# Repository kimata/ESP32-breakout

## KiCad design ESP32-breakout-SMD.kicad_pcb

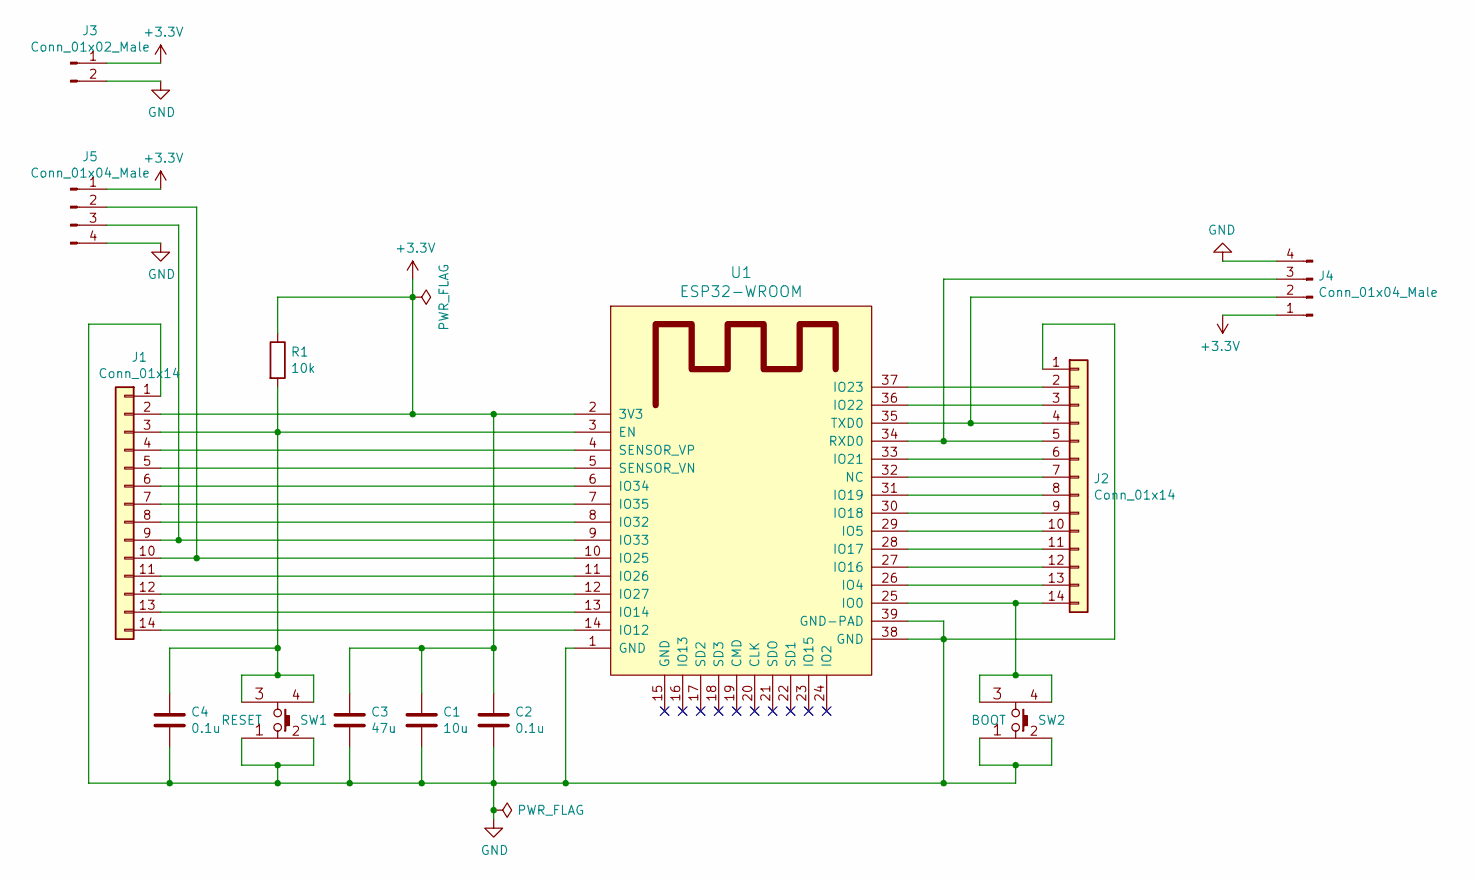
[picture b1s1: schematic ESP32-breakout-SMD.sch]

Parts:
C1: 10u; C_0805_2012Metric_Pad1.15x1.40mm_HandSolder
C2, C4: 0.1u; C_0805_2012Metric_Pad1.15x1.40mm_HandSolder
C3: 47u; C_1206_3216Metric_Pad1.42x1.75mm_HandSolder
J1, J2: Conn_01x14; PinHeader_1x14_P2.54mm_Vertical
J3: Conn_01x02_Male; JST_PH_S2B-PH-SM4-TB_1x02-1MP_P2.00mm_Horizontal
J4, J5: Conn_01x04_Male; JST_PH_S4B-PH-SM4-TB_1x04-1MP_P2.00mm_Horizontal
R1: 10k; R_0805_2012Metric_Pad1.15x1.40mm_HandSolder
SW1: RESET; SKRPACE010
SW2: BOOT; SKRPACE010
U1: ESP32-WROOM

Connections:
+3V3: C1.1, C2.1, C3.1, J1.2, J3.1, J4.1, J5.1, R1.1, U1.2 (3V3)
GND: C1.2, C2.2, C3.2, C4.2, J1.1, J2.1, J3.2, J4.4, J5.4, SW1.1, SW1.2, SW2.1, SW2.2, U1.1 (GND), U1.38 (GND), U1.39 (GND-PAD)
unnamed: C4.1, J1.3, R1.2, SW1.3, SW1.4, U1.3 (EN)
unnamed: J1.4, U1.4 (SENSOR_VP)
unnamed: J1.5, U1.5 (SENSOR_VN)
unnamed: J1.6, U1.6 (IO34)
unnamed: J1.7, U1.7 (IO35)
unnamed: J1.8, U1.8 (IO32)
unnamed: J1.9, J5.3, U1.9 (IO33)
unnamed: J1.10, J5.2, U1.10 (IO25)
unnamed: J1.11, U1.11 (IO26)
unnamed: J1.12, U1.12 (IO27)
unnamed: J1.13, U1.13 (IO14)
unnamed: J1.14, U1.14 (IO12)
unnamed: J2.2, U1.37 (IO23)
unnamed: J2.3, U1.36 (IO22)
unnamed: J2.4, J4.2, U1.35 (TXD0)
unnamed: J2.5, J4.3, U1.34 (RXD0)
unnamed: J2.6, U1.33 (IO21)
unnamed: J2.7, U1.32 (NC)
unnamed: J2.8, U1.31 (IO19)
unnamed: J2.9, U1.30 (IO18)
unnamed: J2.10, U1.29 (IO5)
unnamed: J2.11, U1.28 (IO17)
unnamed: J2.12, U1.27 (IO16)
unnamed: J2.13, U1.26 (IO4)
unnamed: J2.14, SW2.3, SW2.4, U1.25 (IO0)

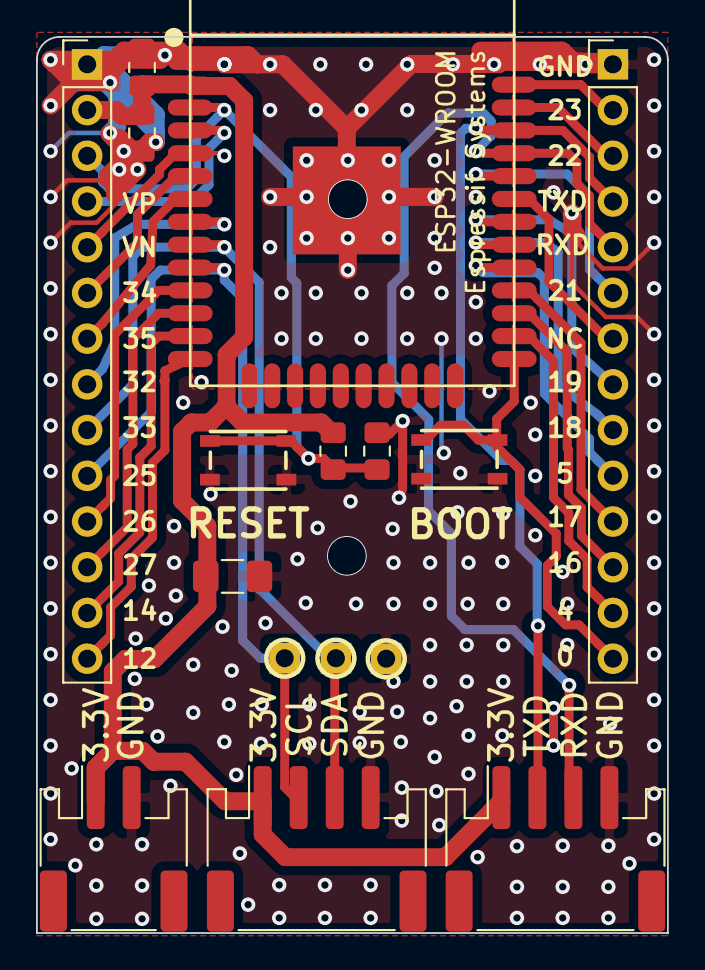
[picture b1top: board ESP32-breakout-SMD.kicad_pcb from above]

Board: 2 copper layers, 35.1 x 49.8 mm, 13 parts (0 on the bottom side), 27 nets.

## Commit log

2019-06-15 とりあえず完成．
2019-07-26 fix: 微修正
2019-07-28 fix: 手はんだしやすいように，スイッチのランドを少し広げた
